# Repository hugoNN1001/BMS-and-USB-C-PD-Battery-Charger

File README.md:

# What is it?

This is a **BMS board** I designed for UNSW Bluesat's Cubesat as part of the **Australian Universities Rocket Competition (AURC)** which takes place in September 2027.

The **USB-C PD charger** is implemented on a separate board due to time constraint before the competition deadline.

The **BQ7791501** is a 3-5 cell stackable, ultra-low power battery pack protector with autonomous cell-balancing and hibernate mode. **Hibernate mode** is important to conserve battery life during long transit and standby time until the launch signal.

<table>
  <tr>
    <td></td>
    <td></td>
  </tr>
  <tr>
    <td></td>
    <td></td>
  </tr>
  <tr>
    <td></td>
    <td></td>
  </tr>
</table>

## Technical

The two main loads are:
- **32 UV LEDs** to cure the resin of the Cubesat's 3D printer payload: In the worst-case, where battery pack voltage is near cut-off and LEDs are at set to output max power, they will draw around **8.5A** continuously
- **Stepper motor**: draws around 0.86A continuously and 1.06A peak

-> **Total current = 8.5A + 1.06A = 9.56A**

**OC1** is set to be **14A at 700ms**, this was chosen due to availability of the sense resistor values and should give us **~30% margin**. However, there is a tolerance of **± 20%** so it could be anywhere between **11.2A to 16.8A**.

**OC2**, as a result, is set at **24A at 350ms**.

The sense resistor is **2.5 mOhms with 0.5% tolerance** (instead of the regular 1%) for accurate current reading. **Kelvin connection** was used so the 2 sense traces carry minimum current. It is also rated up to **3W**, which is well above the calculated power dissipation of **1.44W** at OCD2 current of 24A.

A pair of switches was added to simulate a **hot/cold condition**, which assists in verifying the proper working of the BMS.

A **filter network** was placed close to the sense pins of the protector IC helps to filter noise out of the current reading.

A **jumper shunt** can be removed to enter **hibernate mode**.

## Status

The BMS board is working, **thoroughly verified**, in particular **OV, UV, OTD, UTD, OTC, UTC**.

**OCD1, OCD2, and OCC** is to be verified by using a larger sense resistor value to lower the overcurrent threshold. It is currently too high for the power supply's output current capability.

**Cell-balancing** has also been verified to work.

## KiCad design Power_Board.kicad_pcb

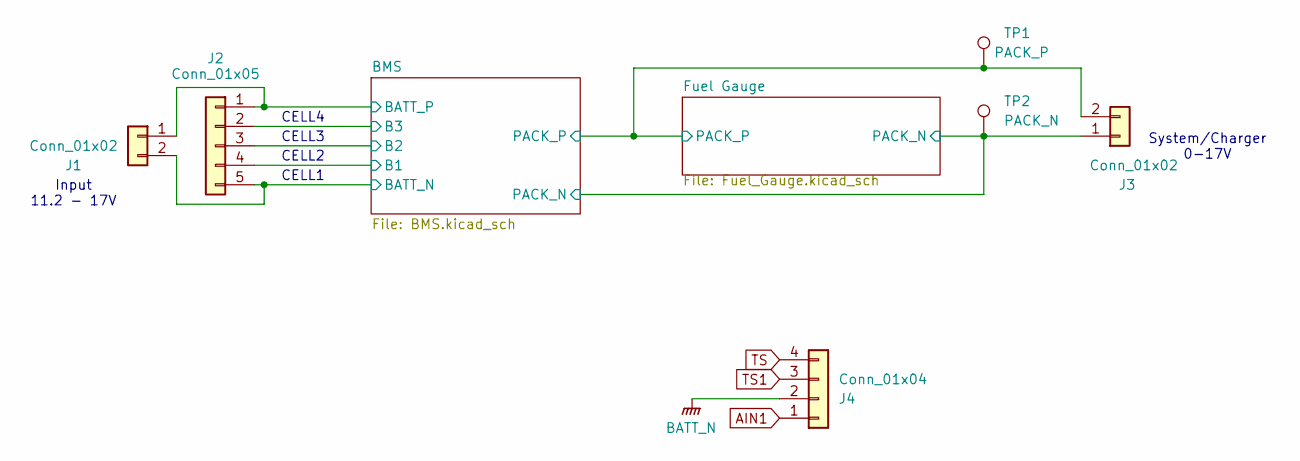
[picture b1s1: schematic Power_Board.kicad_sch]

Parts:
J1: Conn_01x02; AMASS_XT30PW-M
J2: Conn_01x05; SM06B-PASS
J3: Conn_01x02; AMASS_XT30PW-F
J4: Conn_01x04; SM04B-PASS
TP1: PACK_P; TestPoint_Pad_D2.0mm
TP2: PACK_N; TestPoint_Pad_D2.0mm

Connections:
/BMS/B1: J2.4; also elsewhere on the board
/BMS/B2: J2.3; also elsewhere on the board
/BMS/B3: J2.2; also elsewhere on the board
AIN1: J4.1; also elsewhere on the board
BATT_N: J1.2, J2.5, J4.2; also elsewhere on the board
BATT_P: J1.1, J2.1, J3.2, TP1.1 (1_1); also elsewhere on the board
GND: J3.1, TP2.1 (1_1); also elsewhere on the board
TS: J4.4; also elsewhere on the board
TS1: J4.3; also elsewhere on the board

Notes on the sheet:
CELL4
CELL3
CELL1
CELL2
System/Charger 0-17V
Input 11.2 - 17V

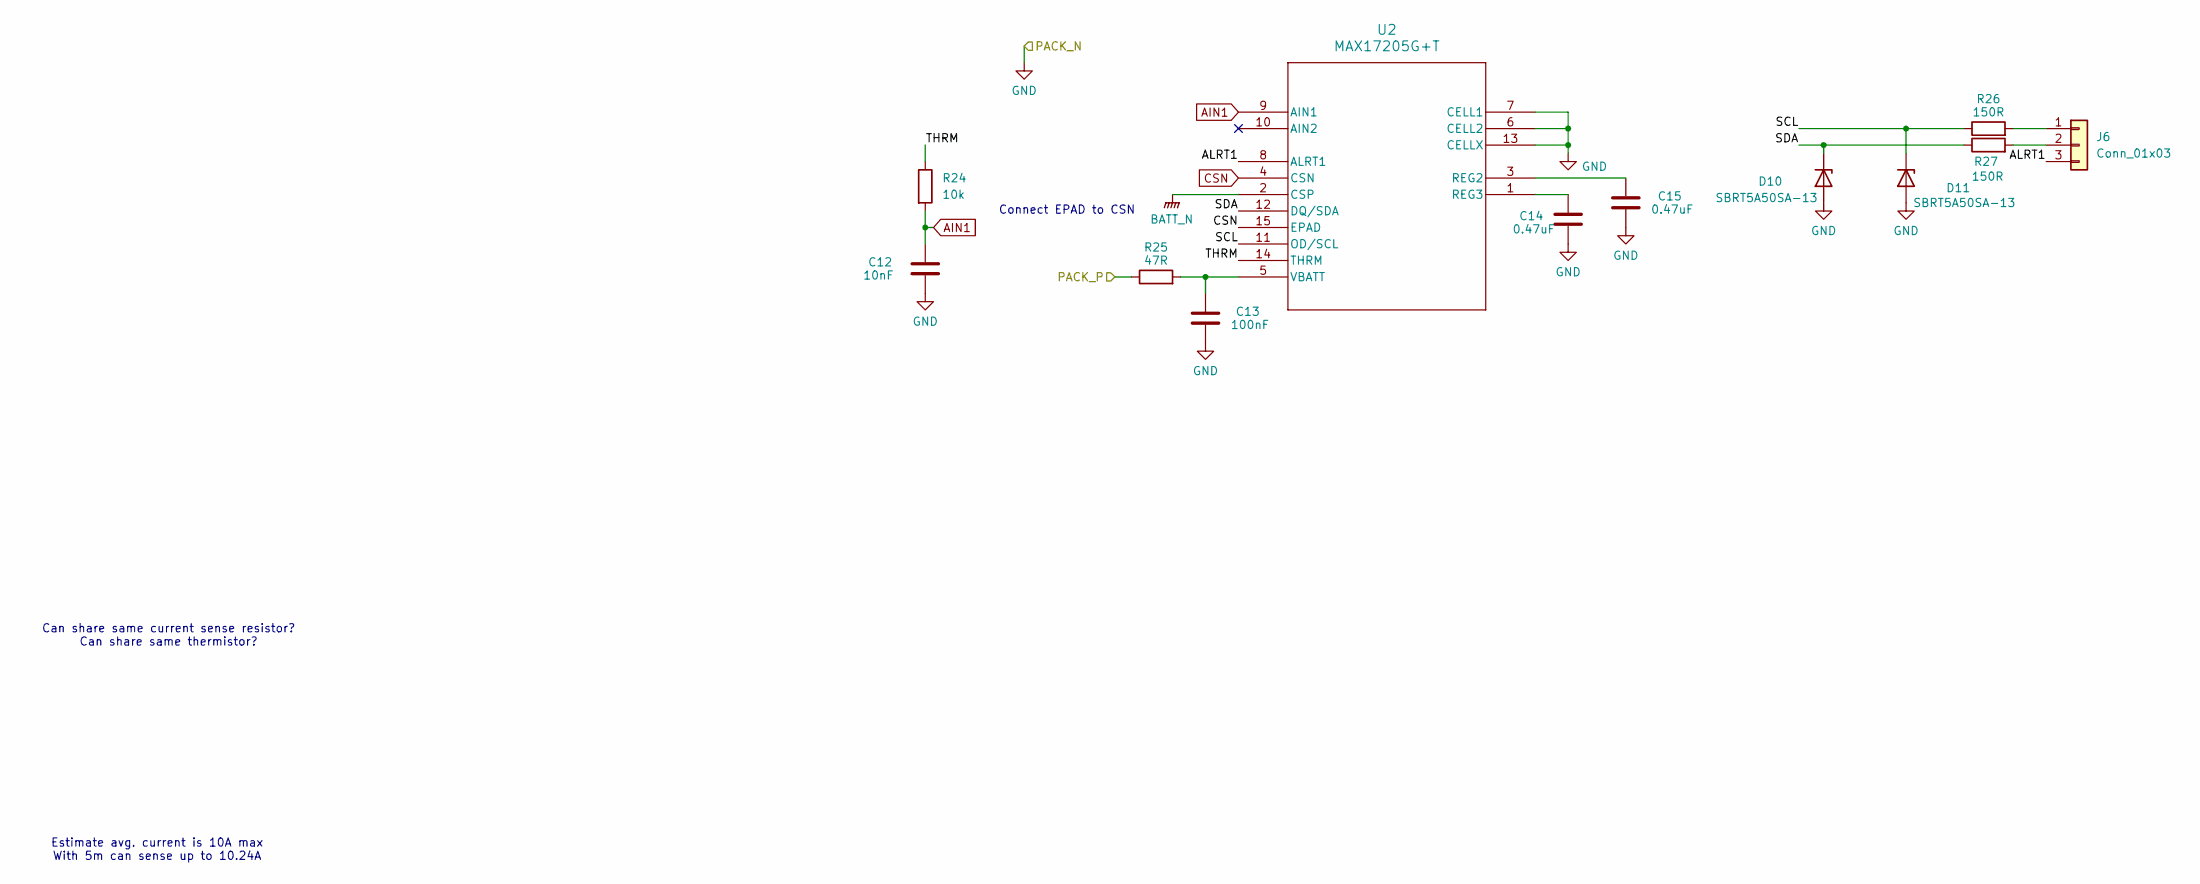
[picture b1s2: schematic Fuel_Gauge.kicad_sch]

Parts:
C12: 10nF; C_0402_1005Metric
C13: 100nF; C_0402_1005Metric
C14, C15: 0.47uF; C_0402_1005Metric
D10, D11: SBRT5A50SA-13; D_SOD-882
J6: Conn_01x03; SM03B-PASS
R24: 10k; R_0402_1005Metric
R25: 47R; R_0402_1005Metric
R26, R27: 150R; R_0402_1005Metric
U2: MAX17205G+T; 21-0137_T1433-2C_MXM

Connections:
/Fuel Gauge/ALRT1: J6.3, U2.8 (ALRT1)
/Fuel Gauge/SCL: D11.1 (K), R26.1, U2.11 (OD/SCL)
/Fuel Gauge/SDA: D10.1 (K), R27.1, U2.12 (DQ/SDA)
/Fuel Gauge/THRM: R24.1, U2.14 (THRM)
AIN1: C12.1, R24.2, U2.9 (AIN1); also elsewhere on the board
BATT_N: U2.2 (CSP); also elsewhere on the board
BATT_P: R25.1; also elsewhere on the board
CSN: U2.4 (CSN), U2.15 (EPAD); also elsewhere on the board
GND: C12.2, C13.2, C14.2, C15.2, D10.2 (A), D11.2 (A), U2.6 (CELL2), U2.7 (CELL1), U2.13 (CELLX); also elsewhere on the board
unnamed: J6.1, R26.2
unnamed: J6.2, R27.2
unnamed: C15.1, U2.3 (REG2)
unnamed: C14.1, U2.1 (REG3)
unnamed: C13.1, R25.2, U2.5 (VBATT)

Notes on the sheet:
Connect EPAD to CSN
Can share same current sense resistor? Can share same thermistor?
Estimate avg. current is 10A max With 5m can sense up to 10.24A

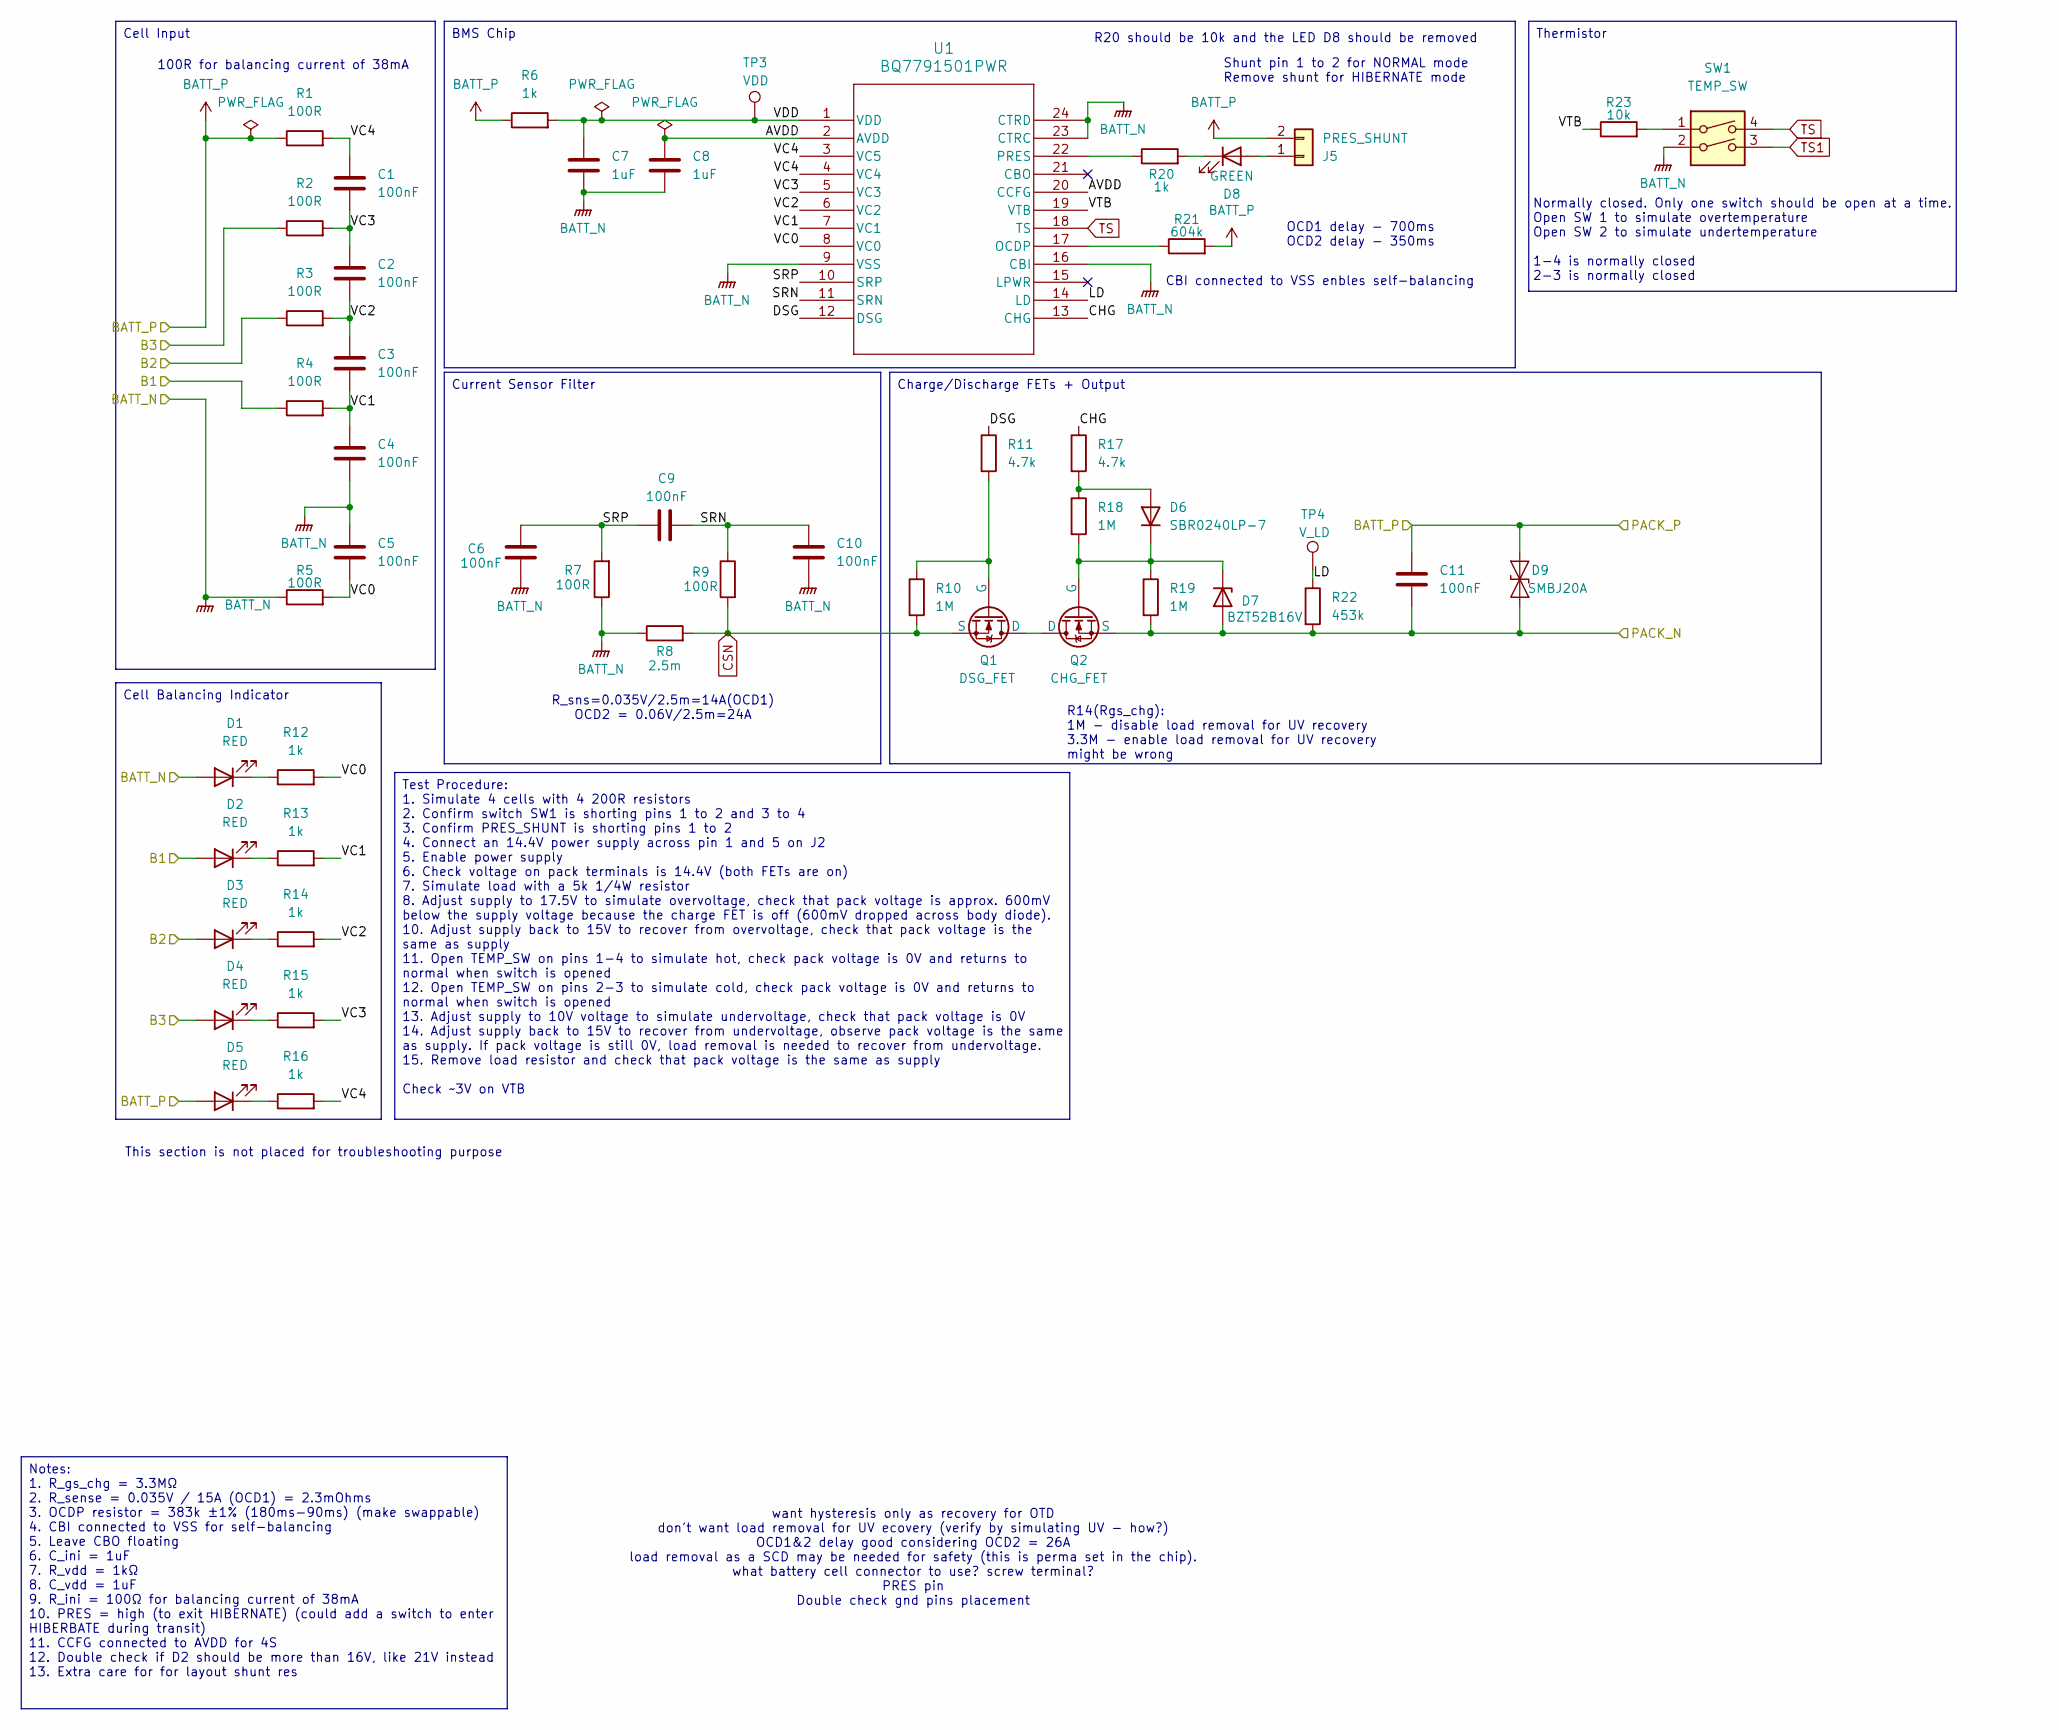
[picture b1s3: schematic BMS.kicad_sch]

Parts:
C1, C2, C3, C4, C5, C6, C9, C10, C11: 100nF; C_0402_1005Metric
C7, C8: 1uF; C_0805_2012Metric
D1, D2, D3, D4, D5: RED; LED_0603_1608Metric
D6: SBR0240LP-7; D_SOD-882
D7: BZT52B16V; D_SOD-123
D8: GREEN; LED_0603_1608Metric
D9: SMBJ20A; D_SMB
J5: PRES_SHUNT; PinHeader_1x02_P2.54mm_Vertical_SMD_Pin1Left
Q1: DSG_FET; PQFN_5x6mm_E_DGS
Q2: CHG_FET; PQFN_5x6mm_E_DGS
R1, R2, R3, R4, R5: 100R; R_0603_1608Metric
R6, R12, R13, R14, R15, R16, R20: 1k; R_0402_1005Metric
R7, R9: 100R; R_0402_1005Metric
R8: 2.5m; R_2512_6332Metric
R10, R18, R19: 1M; R_0402_1005Metric
R11, R17: 4.7k; R_0402_1005Metric
R21: 604k; R_0603_1608Metric
R22: 453k; R_0402_1005Metric
R23: 10k; R_0402_1005Metric
SW1: TEMP_SW; XUNPU DSHP-02-TS-GER
TP3: VDD; TestPoint_Pad_D2.0mm
TP4: V_LD; TestPoint_Pad_D2.0mm
U1: BQ7791501PWR; TSSOP24_PW_TEX

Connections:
/BMS/AVDD: C8.1, U1.2 (AVDD), U1.20 (CCFG)
/BMS/B1: D2.2 (A), R4.1; also elsewhere on the board
/BMS/B2: D3.2 (A), R3.1; also elsewhere on the board
/BMS/B3: D4.2 (A), R2.1; also elsewhere on the board
/BMS/CHG: R17.1, U1.13 (CHG)
/BMS/DSG: R11.1, U1.12 (DSG)
/BMS/LD: R22.1, TP4.1 (1_1), U1.14 (LD)
/BMS/SRN: C9.2, C10.1, R9.1, U1.11 (SRN)
/BMS/SRP: C6.1, C9.1, R7.2, U1.10 (SRP)
/BMS/VC0: C5.2, R5.2, R12.2, U1.8 (VC0)
/BMS/VC1: C3.2, C4.1, R4.2, R13.2, U1.7 (VC1)
/BMS/VC2: C2.2, C3.1, R3.2, R14.2, U1.6 (VC2)
/BMS/VC3: C1.2, C2.1, R2.2, R15.2, U1.5 (VC3)
/BMS/VC4: C1.1, R1.2, R16.2, U1.3 (VC5), U1.4 (VC4)
/BMS/VDD: C7.1, R6.2, TP3.1 (1_1), U1.1 (VDD)
/BMS/VTB: R23.1, U1.19 (VTB)
BATT_N: C4.2, C5.1, C6.2, C7.2, C8.2, C10.2, D1.2 (A), R5.1, R7.1, R8.1, SW1.2, U1.9 (VSS), U1.16 (CBI), U1.23 (CTRC), U1.24 (CTRD); also elsewhere on the board
BATT_P: C11.1, D5.2 (A), D9.2 (A2), J5.2, R1.1, R6.1, R21.2; also elsewhere on the board
CSN: Q1.3 (S), R8.2, R9.2, R10.2; also elsewhere on the board
GND: C11.2, D7.2 (A), D9.1 (A1), Q2.3 (S), R19.2, R22.2; also elsewhere on the board
unnamed: D1.1 (K), R12.1
unnamed: D2.1 (K), R13.1
unnamed: D3.1 (K), R14.1
unnamed: D4.1 (K), R15.1
unnamed: D5.1 (K), R16.1
unnamed: D6.2 (A), R17.2, R18.1
unnamed: D6.1 (K), D7.1 (K), Q2.2 (G), R18.2, R19.1
unnamed: D8.2 (A), J5.1
unnamed: D8.1 (K), R20.2
unnamed: Q1.1 (D), Q2.1 (D)
unnamed: Q1.2 (G), R10.1, R11.2
unnamed: R23.2, SW1.1
unnamed: R21.1, U1.17 (OCDP)
unnamed: R20.1, U1.22 (PRES)
TS: SW1.4, U1.18 (TS); also elsewhere on the board
TS1: SW1.3; also elsewhere on the board

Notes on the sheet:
Shunt pin 1 to 2 for NORMAL mode Remove shunt for HIBERNATE mode
want hysteresis only as recovery for OTD don't want load removal for UV ecovery (verify by simulating UV - how?) OCD1&2 delay good considering OCD2 = 26A load removal as a SCD may be needed for safety (this is perma set in the chip). what battery cell connector to use? screw terminal? PRES pin Doub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
Normally closed. Only one switch should be open at a time. Open SW 1 to simulate overtemperature Open SW 2 to simulate undertemperature 1-4 is normally closed 2-3 is normally closed
100R for balancing current of 38mA
OCD1 delay - 700ms OCD2 delay - 350ms
R14(Rgs_chg): 1M - disable load removal for UV recovery 3.3M - enable load removal for UV recovery might be wrong
R20 should be 10k and the LED D8 should be removed
CBI connected to VSS enbles self-balancing
R_sns=0.035V/2.5m=14A(OCD1) OCD2 = 0.06V/2.5m=24A
This section is not placed for troubleshooting purpose
Test Procedure: 1. Simulate 4 cells with 4 200R resistors 2. Confirm switch SW1 is shorting pins 1 to 2 and 3 to 4 3. Confirm PRES_SHUNT is shorting pins 1 to 2 4. Connect an 14.4V power supply across pin 1 and 5 on J2 5. Enable power supply 6. Check voltage on pack terminals is 14.4V (both FETs ar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
Notes: 1. R_gs_chg = 3.3MΩ 2. R_sense = 0.035V / 15A (OCD1) = 2.3mOhms 3. OCDP resistor = 383k ±1% (180ms-90ms) (make swappable) 4. CBI connected to VSS for self-balancing 5. Leave CBO floating 6. C_ini = 1uF 7. R_vdd = 1kΩ 8. C_vdd = 1uF 9. R_ini = 100Ω for balancing current of 38mA 10. PRES = hig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
Cell Input
Cell Balancing Indicator
Thermistor
Current Sensor Filter
BMS Chip
Charge/Discharge FETs + Output

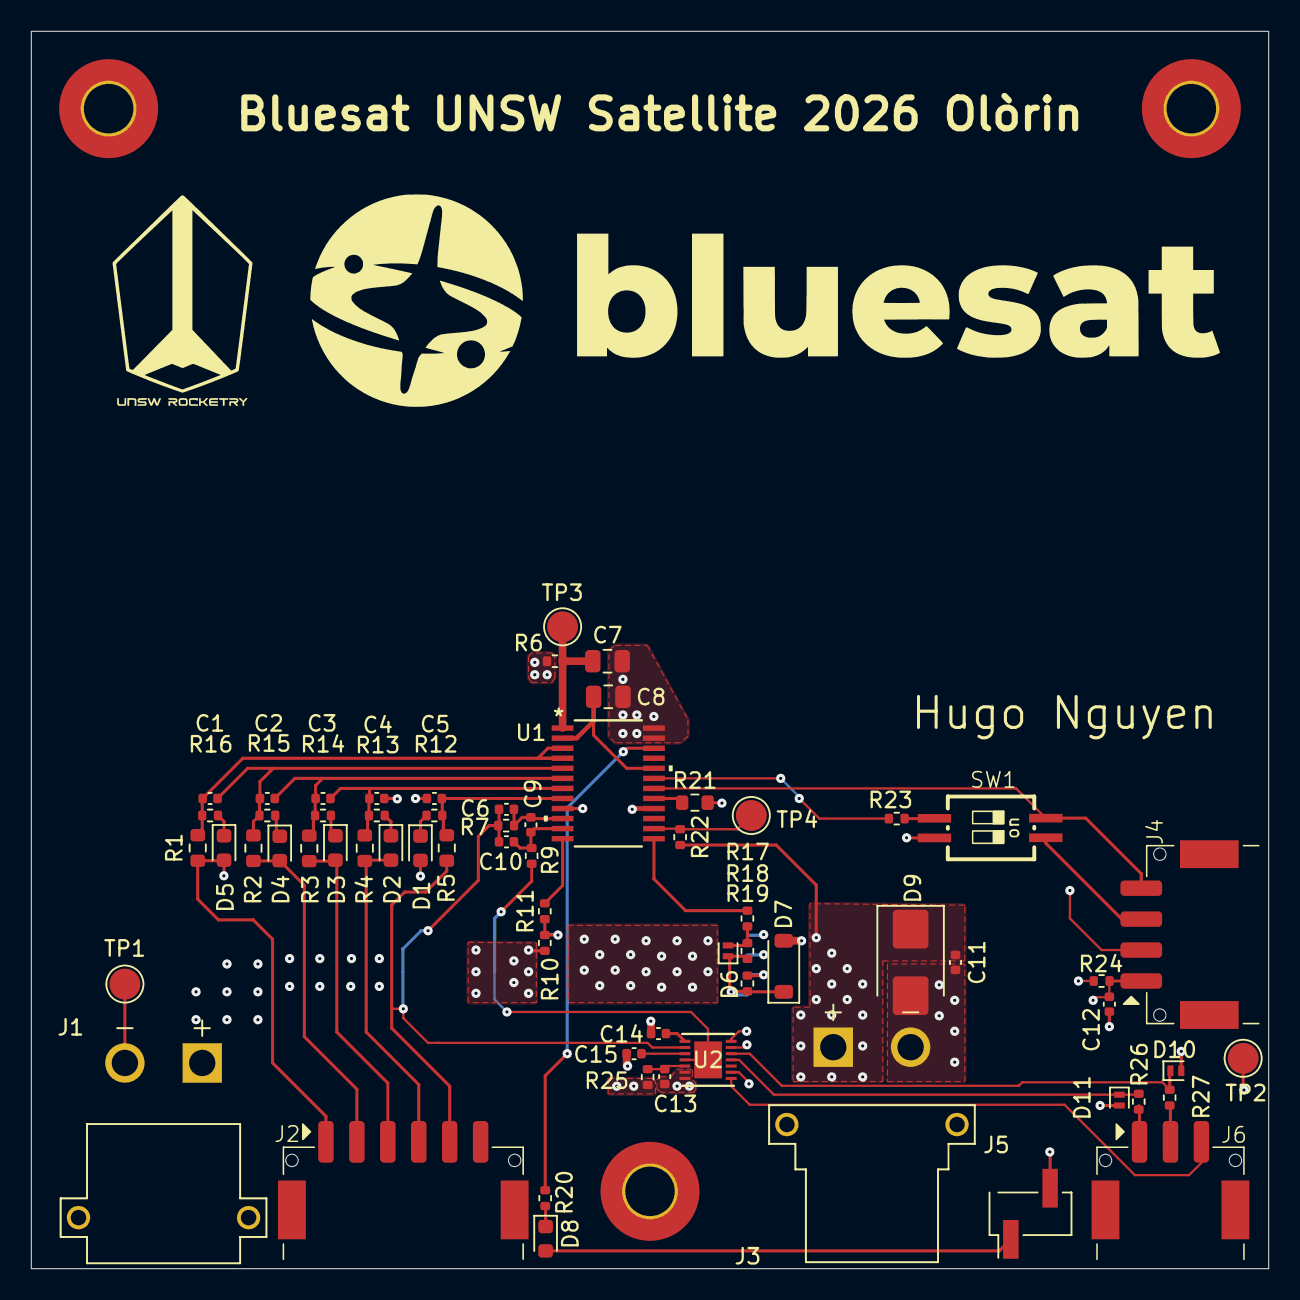
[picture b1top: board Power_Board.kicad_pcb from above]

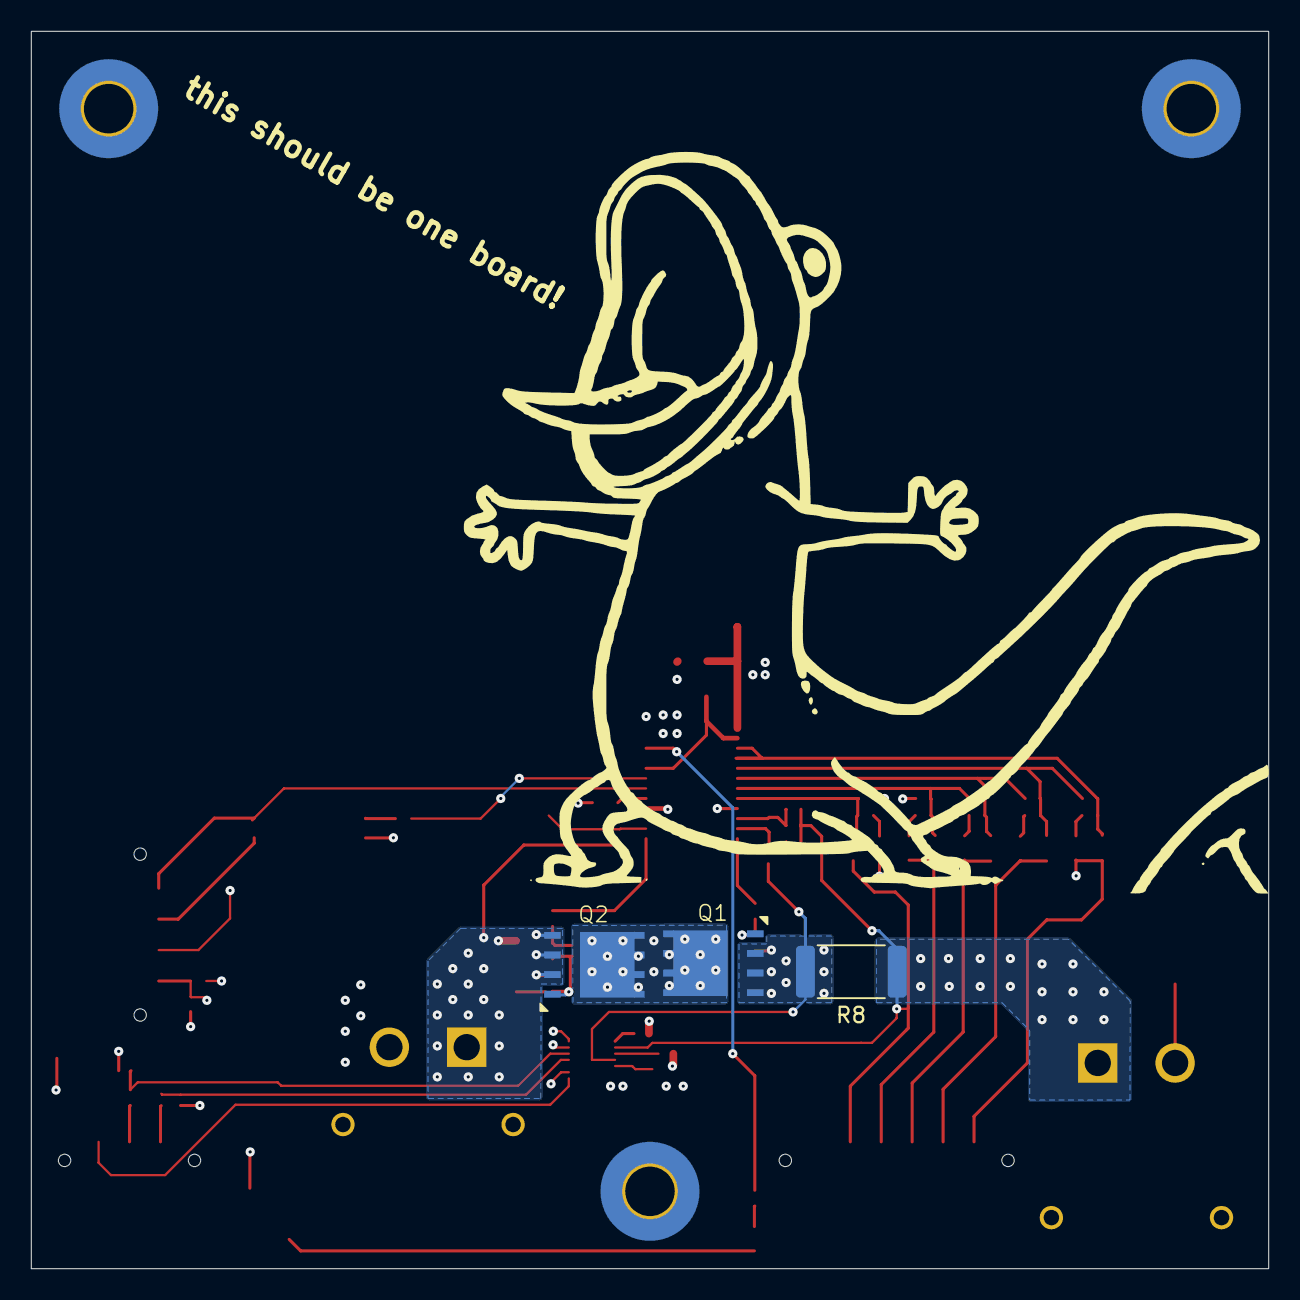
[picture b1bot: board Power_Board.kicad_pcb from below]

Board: 4 copper layers, 80.0 x 80.0 mm, 68 parts (3 on the bottom side), 46 nets.
